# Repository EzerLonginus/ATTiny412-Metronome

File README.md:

# ATTiny412 Metronome
ATTiny412 metronome build
This board is a simple metronome using the ATTiny 412 chip.  The interface includes two push buttons, one rotaty encorder with push button, I2C OLED breakout, and headphone amplifier.  The unit can be powered via a USB-C connector, and has a 6.35mm headphone jack for audio output.
There is also a breakout pins for the UPDI programming, and an additional pin out for the PA3 pin if an external clock source is not used.
The switch button footprints are to allow for either the 12mm or 6mm tactile push buttons.

## Purpose
I pretty much wanted an execuse to play around with the ATTiny Series 1 chips, and wanted to build a fairly simple project that would utilize some of the functionality of the chip.  My original intention was to try to build a fairly functional metronome for as little as possible in parts costs.  There are definitely some corners I could have cut further, but in the end I'm mostly just building it for me, so I don't have to go too wild on cost savings.  That said, I may end up revisiting this project and design this for production.  
Having a rotary encoder with a push button, two additional buttons, a headphone amp, and an I2C breakout does lend itself to other projects besides metronomes (obviously).  So this project may also end up being a testing bed for some other audio related projects I have in mind.

## Schematic

## Layout

## Updates & Fixes
### Version 2
* Changed out headphone amplilfier to LM4808
* Fixed 6.35mm headphone jack footprint
* Added pinout for PA3
* Staggered holes for UPDI for less permananet uploading
* Removed a mounting hole to allow for the DC blocking capacitors

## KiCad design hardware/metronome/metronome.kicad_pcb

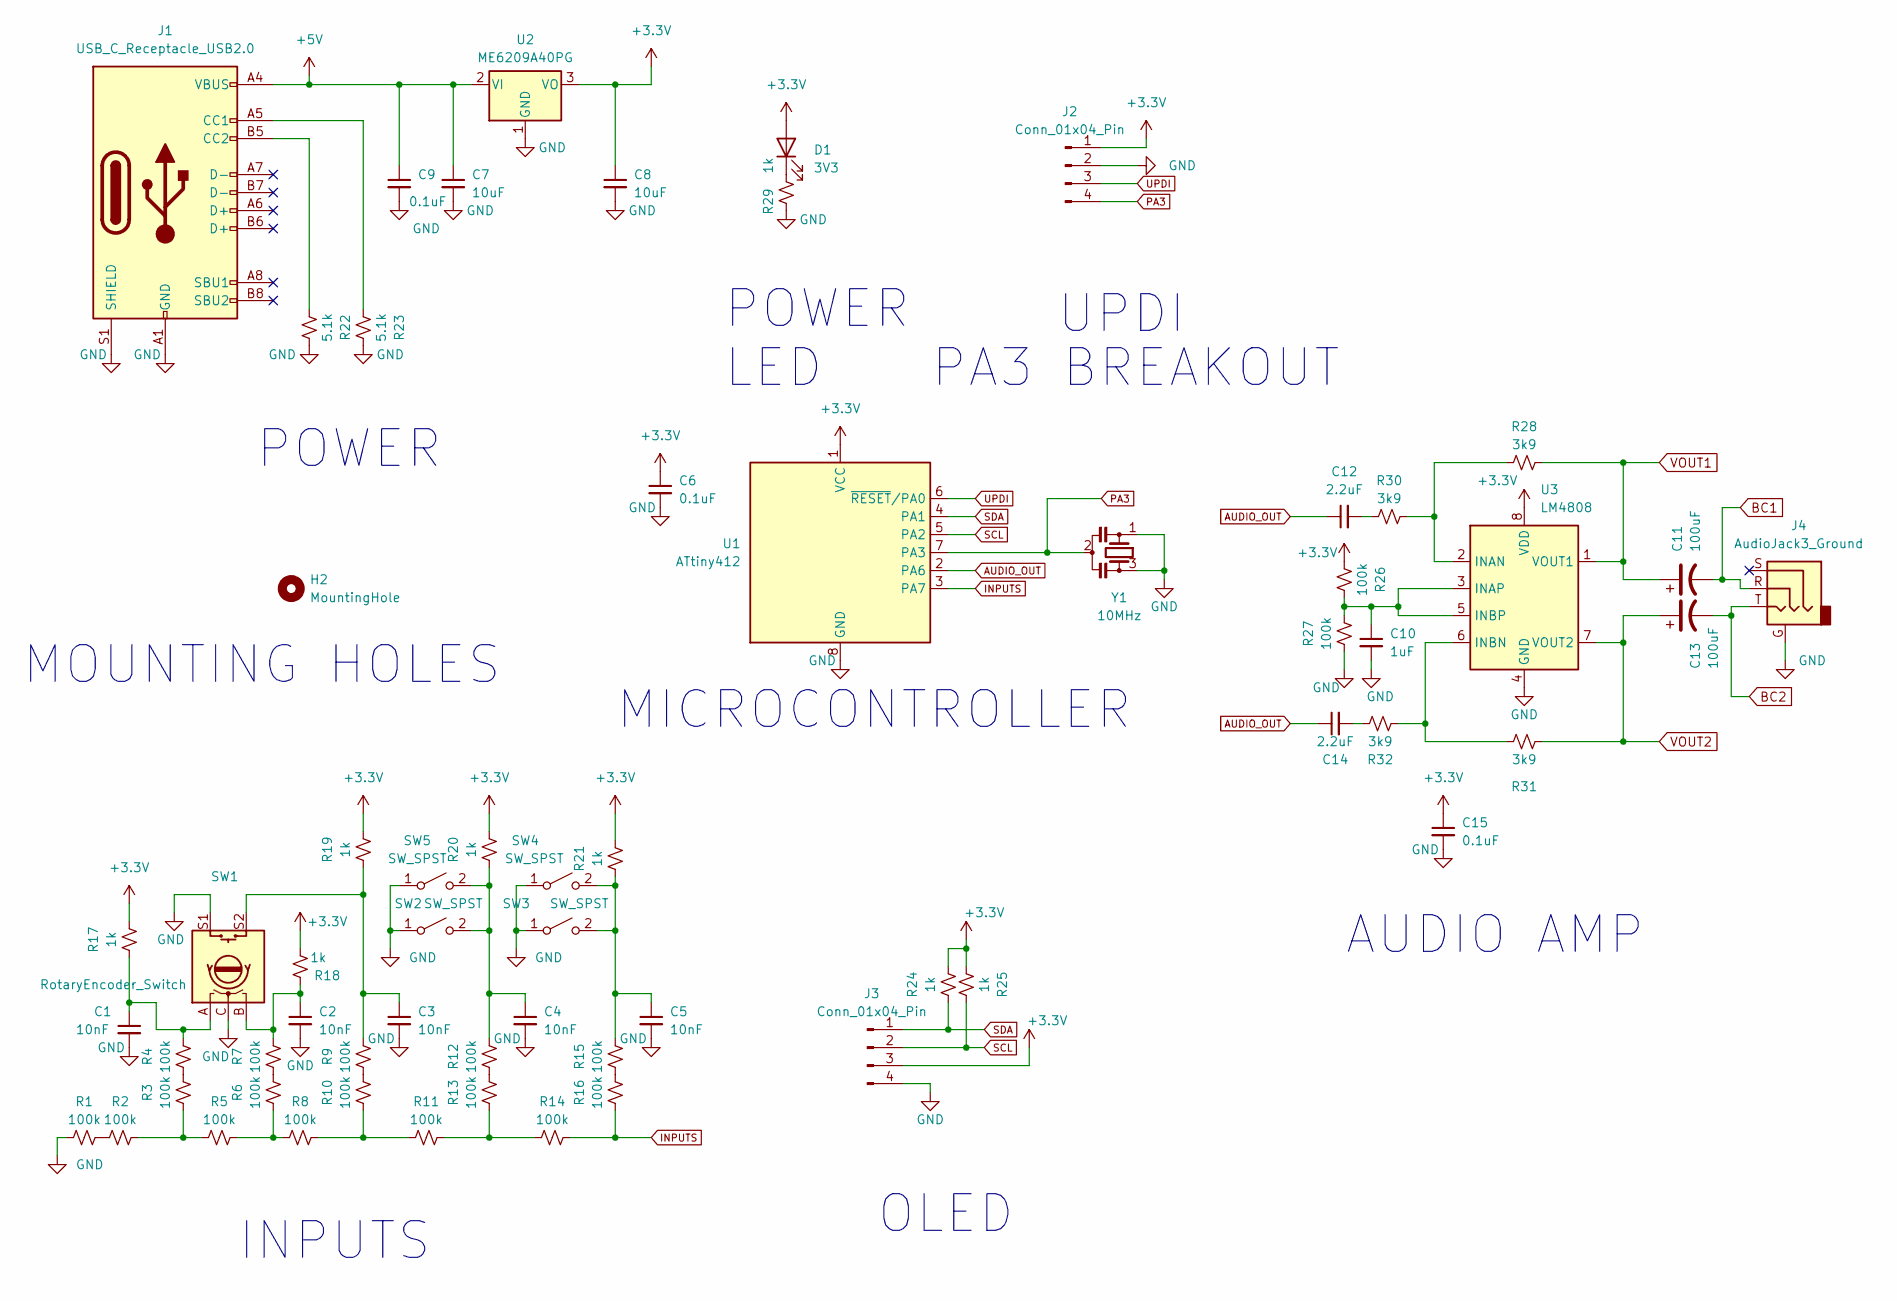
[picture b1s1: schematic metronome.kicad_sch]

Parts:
C1, C2, C3, C4, C5: 10nF; C_0603_1608Metric_Pad1.08x0.95mm_HandSolder
C6, C9, C15: 0.1uF; C_0603_1608Metric_Pad1.08x0.95mm_HandSolder
C7, C8: 10uF; C_0805_2012Metric_Pad1.18x1.45mm_HandSolder
C10: 1uF; C_0603_1608Metric_Pad1.08x0.95mm_HandSolder
C11, C13: 100uF; CP_Elec_6.3x5.4_Nichicon
C12, C14: 2.2uF; C_0805_2012Metric_Pad1.18x1.45mm_HandSolder
D1: 3V3; LED_0603_1608Metric_Pad1.05x0.95mm_HandSolder
H2: MountingHole; MountingHole_2.2mm_M2
J1: USB_C_Receptacle_USB2.0; USB_C_Receptacle_Palconn_UTC16-G
J2: Conn_01x04_Pin; 1x4_2.54mm_pin_staggered
J3: Conn_01x04_Pin; PinHeader_1x04_P2.54mm_Vertical
J4: AudioJack3_Ground; 6.35mm headphone jack PJ-611A
R1, R2, R3, R4, R5, R6, R7, R8, R9, R10, R11, R12, R13, R14, R15, R16, R26, R27: 100k; R_0603_1608Metric_Pad0.98x0.95mm_HandSolder
R17, R18, R19, R20, R21, R24, R25, R29: 1k; R_0603_1608Metric_Pad0.98x0.95mm_HandSolder
R22, R23: 5.1k; R_0603_1608Metric_Pad0.98x0.95mm_HandSolder
R28, R30, R31, R32: 3k9; R_0603_1608Metric_Pad0.98x0.95mm_HandSolder
SW1: RotaryEncoder_Switch; RotaryEncoder_Alps_EC11E-Switch_Vertical_H20mm
SW2, SW3: SW_SPST; SW_PUSH_6mm
SW4, SW5: SW_SPST; SW_PUSH_12mm
U1: ATtiny412; SOIC-8_3.9x4.9mm_P1.27mm
U2: ME6209A40PG; SOT-89-3
U3: LM4808; SOIC-8_3.9x4.9mm_P1.27mm
Y1: 10MHz; 4.5mm_x_2.0mm_MurataElectronics_3Pin_Resonator

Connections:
+3.3V: C6.1, C8.1, C15.1, D1.2 (A), J2.1, J3.3, R17.2, R18.2, R19.2, R20.2, R21.2, R24.2, R25.2, R26.1, U1.1 (VCC), U2.3 (VO), U3.8 (VDD)
+5V: C7.1, C9.1, J1.A4 (VBUS), J1.A9 (VBUS), J1.B4 (VBUS), J1.B9 (VBUS), U2.2 (VI)
AUDIO_OUT: C12.1, C14.1, U1.2 (PA6)
BC1: C11.2, J4.R
BC2: C13.2, J4.T
GND: C1.2, C2.2, C3.2, C4.2, C5.2, C6.2, C7.2, C8.2, C9.2, C10.2, C15.2, J1.A1 (GND), J1.A12 (GND), J1.B1 (GND), J1.B12 (GND), J1.S1 (SHIELD), J2.2, J3.4, J4.G, R1.1, R22.2, R23.1, R27.2, R29.1, SW1.C, SW1.S1, SW2.1 (A), SW3.1 (A), SW4.1 (A), SW5.1 (A), U1.8 (GND), U2.1 (GND), U3.4 (GND), Y1.1, Y1.3
INPUTS: R14.1, R16.2, U1.3 (PA7)
unnamed: C1.1, R4.1, R17.1, SW1.A
unnamed: C2.1, R7.2, R18.1, SW1.B
unnamed: C3.1, R9.2, R19.1, SW1.S2
unnamed: C12.2, R30.1
unnamed: C14.2, R32.1
unnamed: D1.1 (K), R29.2
unnamed: J1.A5 (CC1), R23.2
unnamed: J1.B5 (CC2), R22.1
unnamed: R1.2, R2.2
unnamed: R2.1, R3.1, R5.1
unnamed: R3.2, R4.2
unnamed: R5.2, R6.2, R8.2
unnamed: R6.1, R7.1
unnamed: R9.1, R10.1
unnamed: R8.1, R10.2, R11.2
unnamed: R11.1, R13.2, R14.2
unnamed: R12.1, R13.1
unnamed: R15.1, R16.1
unnamed: C4.1, R12.2, R20.1, SW2.2 (B), SW5.2 (B)
unnamed: C5.1, R15.2, R21.1, SW3.2 (B), SW4.2 (B)
unnamed: R28.1, R30.2, U3.2 (INAN)
unnamed: C10.1, R26.2, R27.1, U3.3 (INAP), U3.5 (INBP)
unnamed: R31.1, R32.2, U3.6 (INBN)
PA3: J2.4, U1.7 (PA3), Y1.2
SCL: J3.2, R25.1, U1.5 (PA2)
SDA: J3.1, R24.1, U1.4 (PA1)
UPDI: J2.3, U1.6 (~RESET/PA0)
VOUT1: C11.1, R28.2, U3.1 (VOUT1)
VOUT2: C13.1, R31.2, U3.7 (VOUT2)

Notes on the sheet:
OLED
PA3 BREAKOUT
UPDI
POWER LED
AUDIO AMP
MOUNTING HOLES
INPUTS
POWER
MICROCONTROLLER

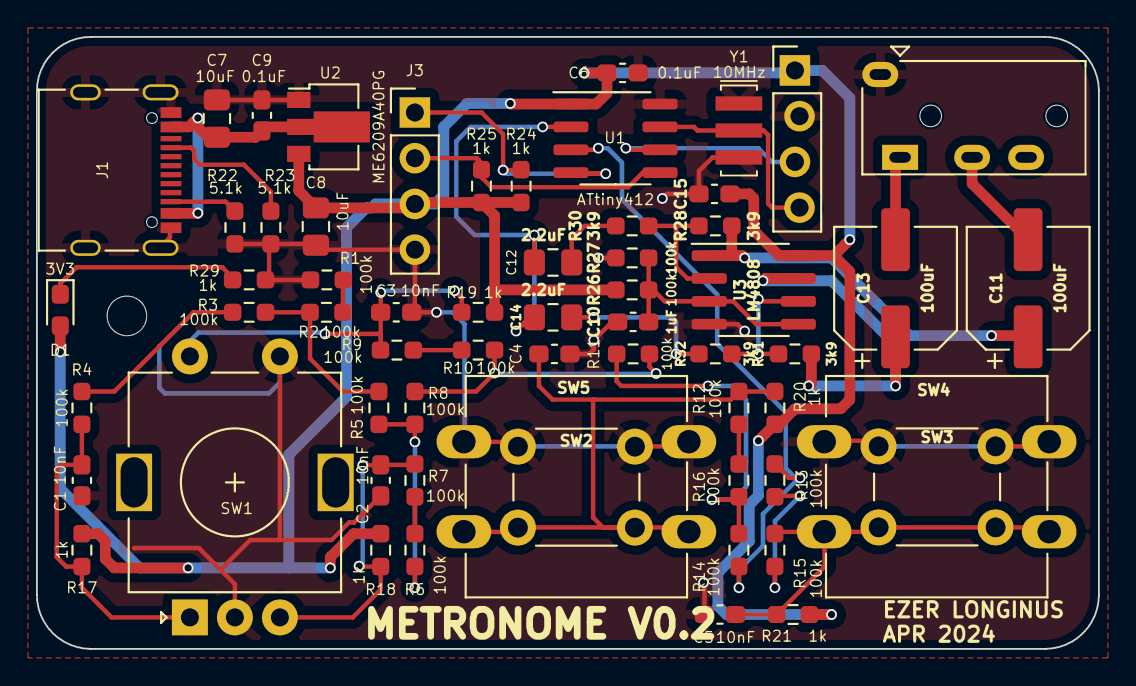
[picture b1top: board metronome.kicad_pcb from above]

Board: 2 copper layers, 59.0 x 34.0 mm, 62 parts (0 on the bottom side), 36 nets.

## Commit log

2024-02-08 initial pcb design
2024-02-08 gerber file zipped
2024-02-08 Design Files and gitignore
2024-02-08 removed extraneous files
2024-02-08 pdf as image test
2024-02-08 design images linked
2024-03-20 Version 02
2024-03-20 Fixed Gerber Files Ommissions
2024-04-25 pin swap
2024-05-23 reduce schematic image
2024-05-23 typo fix
